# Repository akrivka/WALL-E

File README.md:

# WALL-E

For Blacker Hovse Ditch Day 2024 (Caltech tradition), we built a ~70% "real-life" size WALL-E robot, that could be **driven remotely with a PS5 controller, move his head and arms, record and transmit a video feed, speak (faintly)**, and he even had a small storage space in his body (for trash of course!).

Here's my video of him when he was at his best (he's currently sitting in a closet in Blacker to be used as a static showcase project, while I study over in Switzerland...): 

https://github.com/user-attachments/assets/6cdb80cf-8617-4d74-ad6d-1ea3f1ae313b

The model we used was https://www.thingiverse.com/thing:3703555, but we scaled it up by 5/3 which introduced a bunch of challenges. 

**! This repository was used for code-sharing and does not aim to make this project repeatable. Maybe in the future...**

## (rough) List of parts

* Rapsberry Pi 4 (Bluetooth) on Ubuntu 22.04 with ROS2 Humble installed
* PS5 controller
* [RoboClaw 2x15A Motor controller](https://www.basicmicro.com/RoboClaw-2x15A-Motor-Controller_p_10.html)
* [5202 Yellow Jacket Planetary Gear Motor](https://www.gobilda.com/5202-series-yellow-jacket-planetary-gear-motor-26-9-1-ratio-24mm-length-6mm-d-shaft-223-rpm-36mm-gearbox-3-3-5v-encoder/)
* [TowerPro MG996R servos](https://towerpro.com.tw/product/mg996r/)
* [HiLetgo PCA9685 PWM Servo Motor Driver](http://www.hiletgo.com/ProductDetail/2152091.html)
* [Small USB speaker](https://www.amazon.com/shuley-Computer-Speaker-Portable-Sound-bar/dp/B09S3G99HS/ref=sr_1_1)
* some random webcam we found
* 1x 11.1V Zeee LiPo battery (for motor), 1x 7.4V Zee LiPo battery (for servos), some random powerbank (for RPi)

## Some more photos

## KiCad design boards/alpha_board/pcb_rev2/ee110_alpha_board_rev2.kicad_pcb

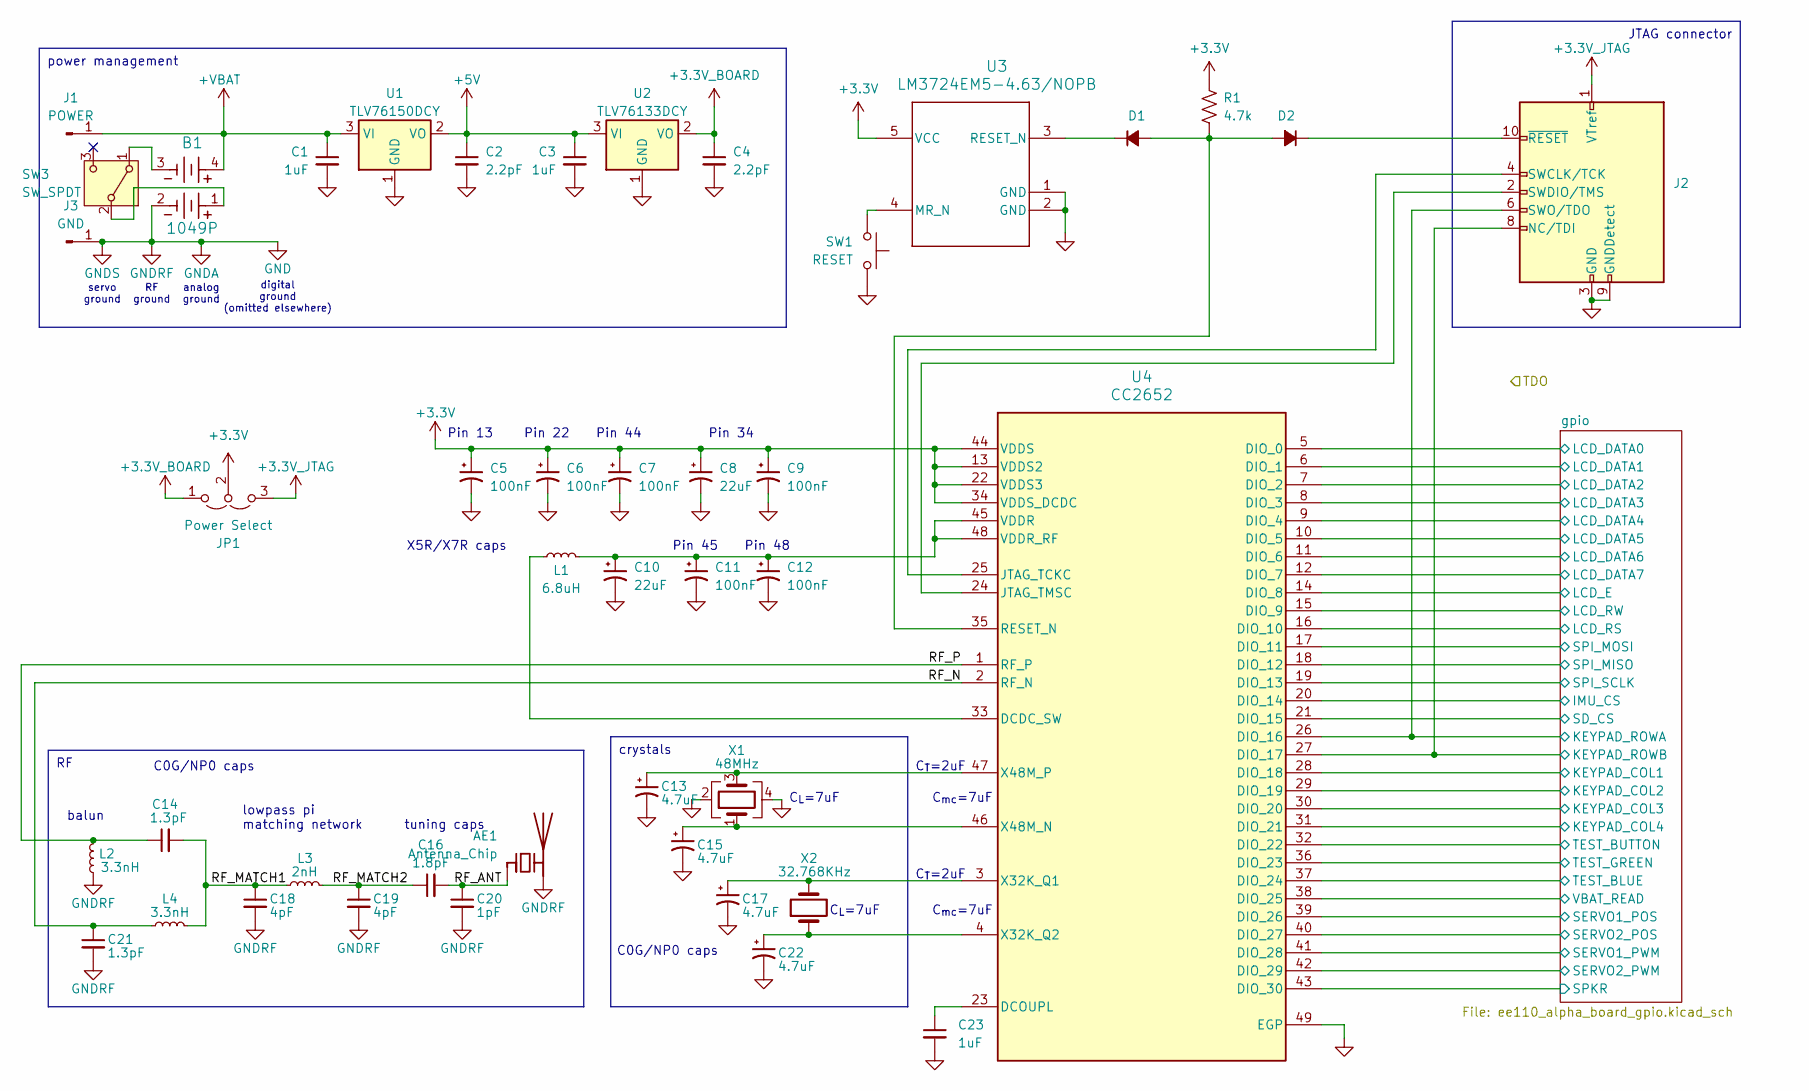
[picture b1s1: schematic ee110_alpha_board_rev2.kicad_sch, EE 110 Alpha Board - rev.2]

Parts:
AE1: Antenna_Chip; EE110_Antenna
B1: 1049P; 1049P_KEY
C1, C3, C23: 1uF; C_0805_2012Metric_Pad1.18x1.45mm_HandSolder
C2, C4: 2.2pF; C_0805_2012Metric_Pad1.18x1.45mm_HandSolder
C5, C6, C7, C9, C11, C12: 100nF; CP_EIA-2012-12_Kemet-R_Pad1.30x1.05mm_HandSolder
C8, C10: 22uF; CP_EIA-2012-12_Kemet-R_Pad1.30x1.05mm_HandSolder
C13, C15, C17, C22: 4.7uF; CP_EIA-2012-12_Kemet-R_Pad1.30x1.05mm_HandSolder
C14, C21: 1.3pF; C_0805_2012Metric_Pad1.18x1.45mm_HandSolder
C16: 1.8pF; C_0805_2012Metric_Pad1.18x1.45mm_HandSolder
C18, C19: 4pF; C_0805_2012Metric_Pad1.18x1.45mm_HandSolder
C20: 1pF; C_0805_2012Metric_Pad1.18x1.45mm_HandSolder
D1, D2: D_Small_Filled; D_SOD-323F
J1: POWER; 1pin
J2: Conn_ARM_JTAG_SWD_10; CON10_2X5_DUK_FTSH_SAI
J3: GND; 1pin
JP1: Power Select; 3pin_jumper
L1: 6.8uH; L_0805_2012Metric_Pad1.15x1.40mm_HandSolder
L2, L4: 3.3nH; L_0805_2012Metric_Pad1.15x1.40mm_HandSolder
L3: 2nH; L_0805_2012Metric_Pad1.15x1.40mm_HandSolder
R1: 4.7k; R_0805_2012Metric_Pad1.20x1.40mm_HandSolder
SW1: RESET; SW_SPST_TL3342
SW3: SW_SPDT; EG1903
U1: TLV76150DCY; SOT-223-3_TabPin2
U2: TLV76133DCY; SOT-223-3_TabPin2
U3: LM3724EM5-4.63/NOPB; SOT-23-5_HandSoldering
U4: CC2652; RGZ0048A_NV
X1: 48MHz; Crystal_SMD_5032-4Pin_5.0x3.2mm
X2: 32.768KHz; Crystal_SMD_3215-2Pin_3.2x1.5mm

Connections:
+3.3V: C5.1, C6.1, C7.1, C8.1, C9.1, JP1.2 (C), R1.1, U3.5 (VCC), U4.13 (VDDS2), U4.22 (VDDS3), U4.34 (VDDS_DCDC), U4.44 (VDDS); also elsewhere on the board
+3.3V_BOARD: C4.1, JP1.1 (A), U2.2 (VO)
+3.3V_JTAG: J2.1 (VTref), JP1.3 (B)
+5V: C2.1, C3.1, U1.2 (VO), U2.3 (VI); also elsewhere on the board
+VBAT: B1.4, C1.1, J1.1, U1.3 (VI); also elsewhere on the board
/RF_ANT: AE1.1 (FEED), C16.2, C20.1
/RF_MATCH1: C14.2, C18.1, L3.1, L4.2
/RF_MATCH2: C16.1, C19.1, L3.2
/RF_N: C21.1, L4.1, U4.2 (RF_N)
/RF_P: C14.1, L2.2, U4.1 (RF_P)
/gpio/IMU_CS: U4.20 (DIO_14); also elsewhere on the board
/gpio/KEYPAD_COL1: U4.28 (DIO_18); also elsewhere on the board
/gpio/KEYPAD_COL2: U4.29 (DIO_19); also elsewhere on the board
/gpio/KEYPAD_COL3: U4.30 (DIO_20); also elsewhere on the board
/gpio/KEYPAD_COL4: U4.31 (DIO_21); also elsewhere on the board
/gpio/KEYPAD_ROWA: J2.6 (SWO/TDO), U4.26 (DIO_16); also elsewhere on the board
/gpio/KEYPAD_ROWB: J2.8 (NC/TDI), U4.27 (DIO_17); also elsewhere on the board
/gpio/LCD_DATA0: U4.5 (DIO_0); also elsewhere on the board
/gpio/LCD_DATA1: U4.6 (DIO_1); also elsewhere on the board
/gpio/LCD_DATA2: U4.7 (DIO_2); also elsewhere on the board
/gpio/LCD_DATA3: U4.8 (DIO_3); also elsewhere on the board
/gpio/LCD_DATA4: U4.9 (DIO_4); also elsewhere on the board
/gpio/LCD_DATA5: U4.10 (DIO_5); also elsewhere on the board
/gpio/LCD_DATA6: U4.11 (DIO_6); also elsewhere on the board
/gpio/LCD_DATA7: U4.12 (DIO_7); also elsewhere on the board
/gpio/LCD_E: U4.14 (DIO_8); also elsewhere on the board
/gpio/LCD_RS: U4.16 (DIO_10); also elsewhere on the board
/gpio/LCD_RW: U4.15 (DIO_9); also elsewhere on the board
/gpio/SD_CS: U4.21 (DIO_15); also elsewhere on the board
/gpio/SERVO1_POS: U4.39 (DIO_26); also elsewhere on the board
/gpio/SERVO1_PWM: U4.41 (DIO_28); also elsewhere on the board
/gpio/SERVO2_POS: U4.40 (DIO_27); also elsewhere on the board
/gpio/SERVO2_PWM: U4.42 (DIO_29); also elsewhere on the board
/gpio/SPI_MISO: U4.18 (DIO_12); also elsewhere on the board
/gpio/SPI_MOSI: U4.17 (DIO_11); also elsewhere on the board
/gpio/SPI_SCLK: U4.19 (DIO_13); also elsewhere on the board
/gpio/SPKR: U4.43 (DIO_30); also elsewhere on the board
/gpio/TEST_BLUE: U4.37 (DIO_24); also elsewhere on the board
/gpio/TEST_BUTTON: U4.32 (DIO_22); also elsewhere on the board
/gpio/TEST_GREEN: U4.36 (DIO_23); also elsewhere on the board
/gpio/VBAT_READ: U4.38 (DIO_25); also elsewhere on the board
GND: AE1.2 (PCB_Trace), B1.2, C1.2, C2.2, C3.2, C4.2, C5.2, C6.2, C7.2, C8.2, C9.2, C10.2, C11.2, C12.2, C13.2, C15.2, C17.2, C18.2, C19.2, C20.2, C21.2, C22.2, C23.2, J2.3 (GND), J2.5 (GND), J2.9 (GNDDetect), J3.1, L2.1, SW1.2, U1.1 (GND), U2.1 (GND), U3.1 (GND), U3.2 (GND), U4.49 (EGP), X1.2, X1.4; also elsewhere on the board
unnamed: D1.2 (A), D2.2 (A), R1.2, U4.35 (RESET_N)
unnamed: D1.1 (K), U3.3 (RESET_N)
unnamed: D2.1 (K), J2.10 (~RESET)
unnamed: J2.4 (SWCLK/TCK), U4.25 (JTAG_TCKC)
unnamed: J2.2 (SWDIO/TMS), U4.24 (JTAG_TMSC)
unnamed: B1.3, SW3.1 (A)
unnamed: B1.1, SW3.2 (B)
unnamed: SW1.1, U3.4 (MR_N)
unnamed: L1.1, U4.33 (DCDC_SW)
unnamed: C23.1, U4.23 (DCOUPL)
unnamed: C10.1, C11.1, C12.1, L1.2, U4.45 (VDDR), U4.48 (VDDR_RF)
unnamed: C17.1, U4.3 (X32K_Q1), X2.2
unnamed: C22.1, U4.4 (X32K_Q2), X2.1
unnamed: C15.1, U4.46 (X48M_N), X1.1
unnamed: C13.1, U4.47 (X48M_P), X1.3

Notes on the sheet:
power management
JTAG connector
crystals
Pin 22
C_{mc}=7uF
tuning caps
Pin 44
lowpass pi matching network
C0G/NP0 caps
X5R/X7R caps
C_{T}=2uF
RF ground
Pin 48
Pin 45
C_{L}=7uF
Pin 34
servo ground
analog ground
digital ground (omitted elsewhere)
Pin 13
balun

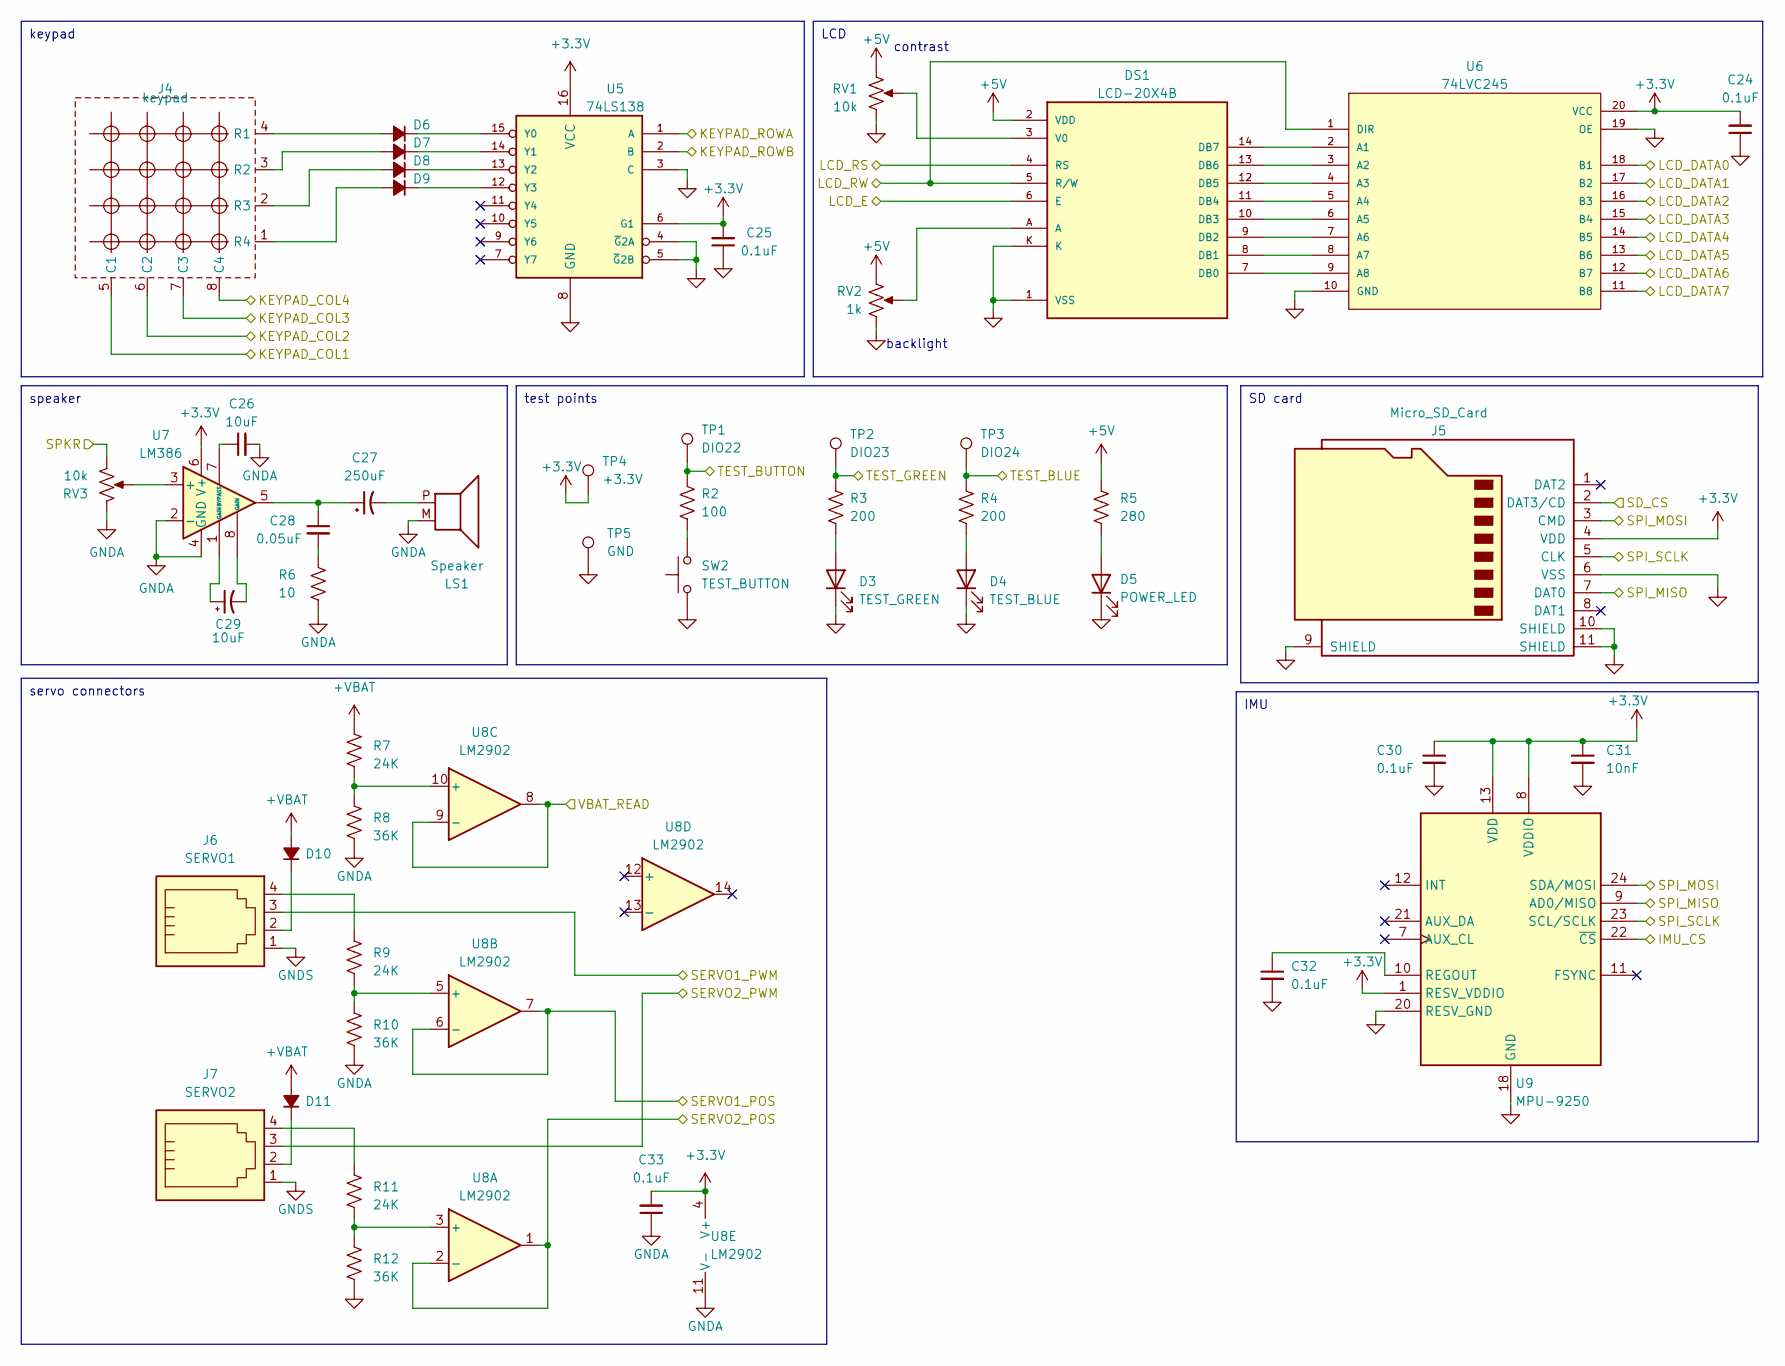
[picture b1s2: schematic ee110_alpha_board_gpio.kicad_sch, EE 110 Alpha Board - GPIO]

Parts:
C24, C25, C30, C32, C33: 0.1uF; C_0805_2012Metric_Pad1.18x1.45mm_HandSolder
C26: 10uF; C_0805_2012Metric_Pad1.18x1.45mm_HandSolder
C27: 250uF; CP_EIA-2012-12_Kemet-R_Pad1.30x1.05mm_HandSolder
C28: 0.05uF; C_0805_2012Metric_Pad1.18x1.45mm_HandSolder
C29: 10uF; CP_EIA-2012-12_Kemet-R_Pad1.30x1.05mm_HandSolder
C31: 10nF; C_0805_2012Metric_Pad1.18x1.45mm_HandSolder
D3: TEST_GREEN; LED_0805_2012Metric_Pad1.15x1.40mm_HandSolder
D4: TEST_BLUE; LED_0805_2012Metric_Pad1.15x1.40mm_HandSolder
D5: POWER_LED; LED_D3.0mm
D6, D7, D8, D9: D_Small_Filled; D_SOD-323F
D10, D11: D_Small_Filled; D_DO-15_P12.70mm_Horizontal
DS1: LCD-20X4B; WINSTAR-WH1604A; PARTREV N/A
J4: keypad; 4x4_Keypad
J5: Micro_SD_Card; microSD_HC_Hirose_DM3D-SF
J6: SERVO1; JST_XH_S4B-XH-A-1_1x04_P2.50mm_Horizontal
J7: SERVO2; JST_XH_S4B-XH-A-1_1x04_P2.50mm_Horizontal
LS1: Speaker; SPKR_CVS-1508
R2: 100; R_0805_2012Metric_Pad1.20x1.40mm_HandSolder
R3, R4: 200; R_0805_2012Metric_Pad1.20x1.40mm_HandSolder
R5: 280; R_0805_2012Metric_Pad1.20x1.40mm_HandSolder
R6: 10; R_0805_2012Metric_Pad1.20x1.40mm_HandSolder
R7, R9, R11: 24K; R_0805_2012Metric_Pad1.20x1.40mm_HandSolder
R8, R10, R12: 36K; R_0805_2012Metric_Pad1.20x1.40mm_HandSolder
RV1, RV3: 10k; Potentiometer_Bourns_3296P_Horizontal
RV2: 1k; Potentiometer_Bourns_3296P_Horizontal
SW2: TEST_BUTTON; SW_SPST_TL3342
TP1: DIO22; TestPoint_THTPad_2.0x2.0mm_Drill1.0mm
TP2: DIO23; TestPoint_THTPad_2.0x2.0mm_Drill1.0mm
TP3: DIO24; TestPoint_THTPad_2.0x2.0mm_Drill1.0mm
TP4: +3.3V; TestPoint_THTPad_2.0x2.0mm_Drill1.0mm
TP5: GND; TestPoint_THTPad_2.0x2.0mm_Drill1.0mm
U5: 74LS138; SOIC-16_3.9x9.9mm_P1.27mm
U6: 74LVC245; SOIC-20W_7.5x15.4mm_P1.27mm
U7: LM386; DIP-8_W7.62mm
U8: LM2902; SOIC-14_3.9x8.7mm_P1.27mm
U9: MPU-9250; QFN-24-1EP_3x3mm_P0.4mm_EP1.75x1.6mm

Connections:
+3.3V: C24.2, C25.2, C30.1, C31.1, C33.2, J5.4 (VDD), TP4.1, U5.6 (G1), U5.16 (VCC), U6.20 (VCC), U7.6 (V+), U8.4 (V+), U9.1 (RESV_VDDIO), U9.8 (VDDIO), U9.13 (VDD); also elsewhere on the board
+5V: DS1.2 (VDD), R5.1, RV1.1, RV2.1; also elsewhere on the board
+VBAT: D10.2 (A), D11.2 (A), R7.1; also elsewhere on the board
/gpio/IMU_CS: U9.22 (~CS); also elsewhere on the board
/gpio/KEYPAD_COL1: J4.5 (C1); also elsewhere on the board
/gpio/KEYPAD_COL2: J4.6 (C2); also elsewhere on the board
/gpio/KEYPAD_COL3: J4.7 (C3); also elsewhere on the board
/gpio/KEYPAD_COL4: J4.8 (C4); also elsewhere on the board
/gpio/KEYPAD_ROWA: U5.1 (A); also elsewhere on the board
/gpio/KEYPAD_ROWB: U5.2 (B); also elsewhere on the board
/gpio/LCD_DATA0: U6.18 (B1); also elsewhere on the board
/gpio/LCD_DATA1: U6.17 (B2); also elsewhere on the board
/gpio/LCD_DATA2: U6.16 (B3); also elsewhere on the board
/gpio/LCD_DATA3: U6.15 (B4); also elsewhere on the board
/gpio/LCD_DATA4: U6.14 (B5); also elsewhere on the board
/gpio/LCD_DATA5: U6.13 (B6); also elsewhere on the board
/gpio/LCD_DATA6: U6.12 (B7); also elsewhere on the board
/gpio/LCD_DATA7: U6.11 (B8); also elsewhere on the board
/gpio/LCD_E: DS1.6 (E); also elsewhere on the board
/gpio/LCD_RS: DS1.4 (RS); also elsewhere on the board
/gpio/LCD_RW: DS1.5 (R/W), U6.1 (DIR); also elsewhere on the board
/gpio/SD_CS: J5.2 (DAT3/CD); also elsewhere on the board
/gpio/SERVO1_POS: U8.6 (-), U8.7; also elsewhere on the board
/gpio/SERVO1_PWM: J6.3; also elsewhere on the board
/gpio/SERVO2_POS: U8.1, U8.2 (-); also elsewhere on the board
/gpio/SERVO2_PWM: J7.3; also elsewhere on the board
/gpio/SPI_MISO: J5.7 (DAT0), U9.9 (AD0/MISO); also elsewhere on the board
/gpio/SPI_MOSI: J5.3 (CMD), U9.24 (SDA/MOSI); also elsewhere on the board
/gpio/SPI_SCLK: J5.5 (CLK), U9.23 (SCL/SCLK); also elsewhere on the board
/gpio/SPKR: RV3.3; also elsewhere on the board
/gpio/TEST_BLUE: R4.2, TP3.1; also elsewhere on the board
/gpio/TEST_BUTTON: R2.2, TP1.1; also elsewhere on the board
/gpio/TEST_GREEN: R3.2, TP2.1; also elsewhere on the board
/gpio/VBAT_READ: U8.8, U8.9 (-); also elsewhere on the board
GND: C24.1, C25.1, C26.2, C30.2, C31.2, C32.2, C33.1, D3.1 (K), D4.1 (K), D5.1 (K), DS1.1 (VSS), DS1.K, J5.6 (VSS), J5.9 (SHIELD), J5.10 (SHIELD), J5.11 (SHIELD), J6.1, J7.1, LS1.M (2), R6.2, R8.2, R10.2, R12.2, RV1.3, RV2.3, RV3.1, SW2.1, TP5.1, U5.3 (C), U5.4 (~G2A), U5.5 (~G2B), U5.8 (GND), U6.10 (GND), U6.19 (OE), U7.2 (-), U7.4 (GND), U8.11 (V-), U9.18 (GND), U9.20 (RESV_GND); also elsewhere on the board
unnamed: C27.1, C28.1, U7.5
unnamed: C28.2, R6.1
unnamed: C29.1, U7.1 (GAIN)
unnamed: C29.2, U7.8 (GAIN)
unnamed: D3.2 (A), R3.1
unnamed: D4.2 (A), R4.1
unnamed: D5.2 (A), R5.2
unnamed: D6.2 (A), J4.4 (R1)
unnamed: D6.1 (K), U5.15 (Y0)
unnamed: D7.2 (A), J4.3 (R2)
unnamed: D7.1 (K), U5.14 (Y1)
unnamed: D8.2 (A), J4.2 (R3)
unnamed: D8.1 (K), U5.13 (Y2)
unnamed: D9.2 (A), J4.1 (R4)
unnamed: D9.1 (K), U5.12 (Y3)
unnamed: D10.1 (K), J6.2
unnamed: D11.1 (K), J7.2
unnamed: DS1.7 (DB0), U6.9 (A8)
unnamed: DS1.8 (DB1), U6.8 (A7)
unnamed: DS1.9 (DB2), U6.7 (A6)
unnamed: DS1.10 (DB3), U6.6 (A5)
unnamed: DS1.11 (DB4), U6.5 (A4)
unnamed: DS1.12 (DB5), U6.4 (A3)
unnamed: DS1.13 (DB6), U6.3 (A2)
unnamed: DS1.14 (DB7), U6.2 (A1)
unnamed: DS1.A, RV2.2
unnamed: DS1.3 (V0), RV1.2
unnamed: J6.4, R9.1
unnamed: J7.4, R11.1
unnamed: C27.2, LS1.P (1)
unnamed: R2.1, SW2.2
unnamed: RV3.2, U7.3 (+)
unnamed: C26.1, U7.7 (BYPASS)
unnamed: R11.2, R12.1, U8.3 (+)
unnamed: R9.2, R10.1, U8.5 (+)
unnamed: R7.2, R8.1, U8.10 (+)
unnamed: C32.1, U9.10 (REGOUT)

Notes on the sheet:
keypad
SD card
servo connectors
speaker
test points
LCD
IMU
backlight
contrast

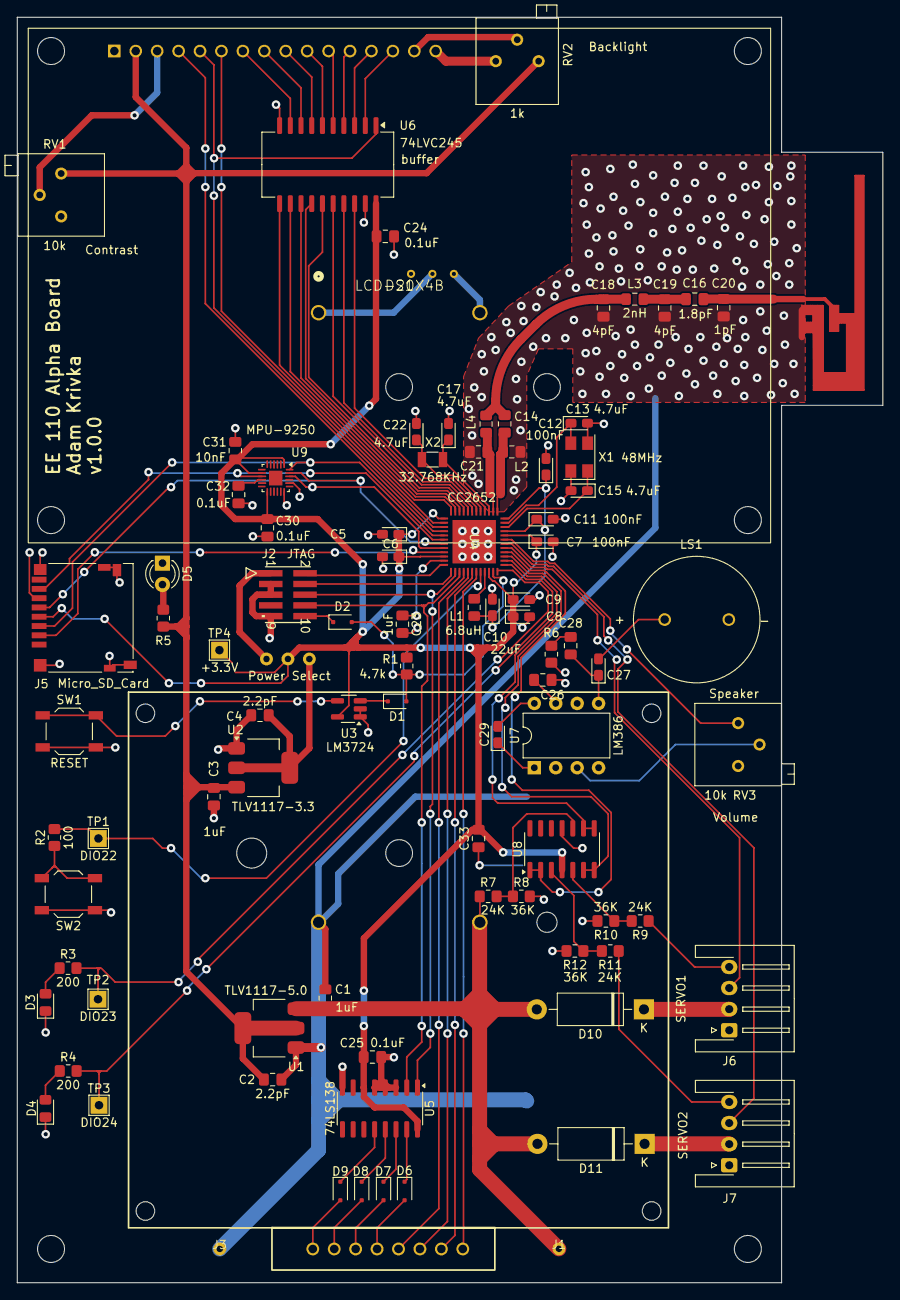
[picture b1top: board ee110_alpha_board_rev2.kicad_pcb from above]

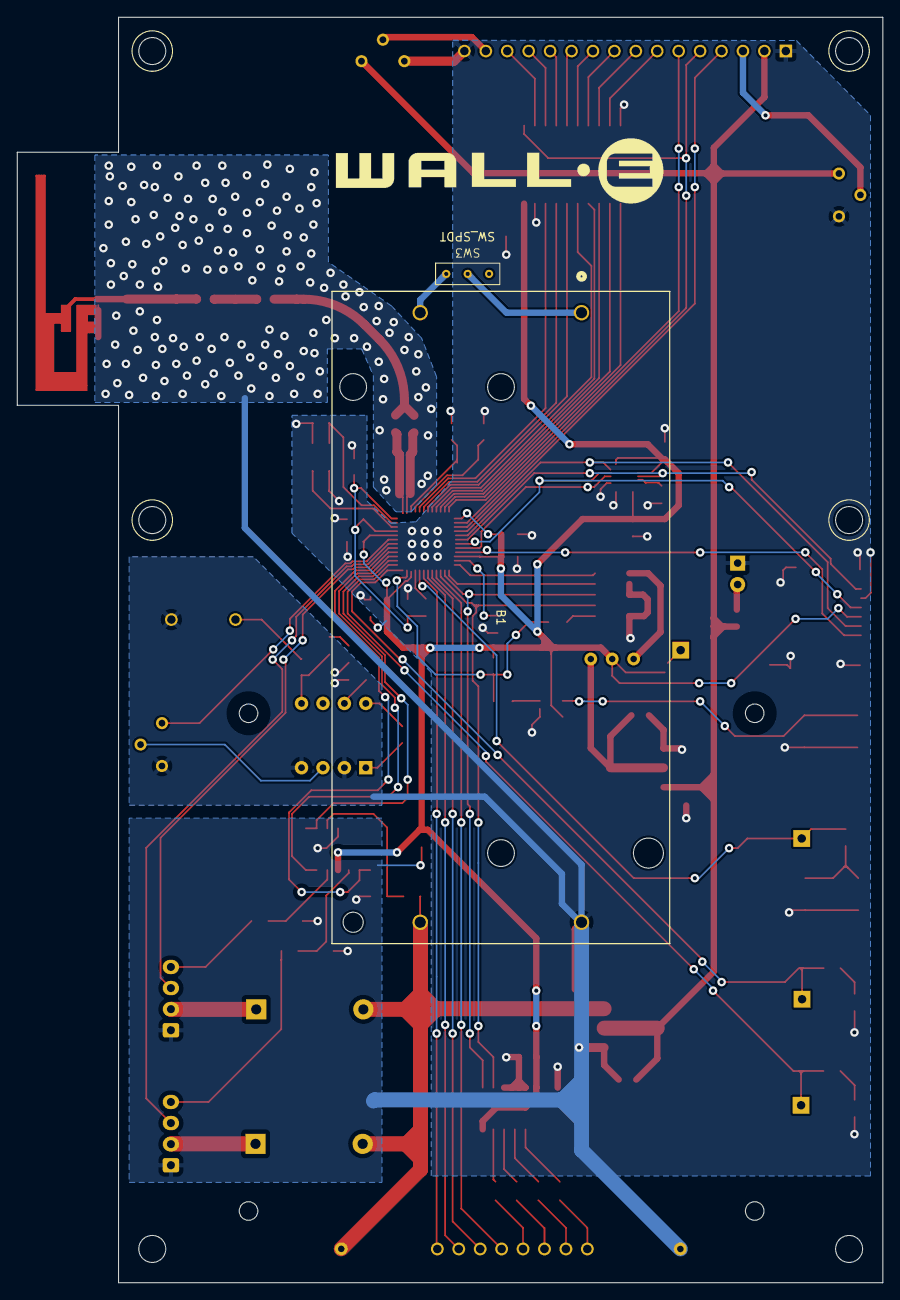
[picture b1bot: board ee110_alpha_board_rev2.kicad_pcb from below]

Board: 2 copper layers, 102.6 x 150.0 mm, 93 parts (2 on the bottom side), 94 nets.

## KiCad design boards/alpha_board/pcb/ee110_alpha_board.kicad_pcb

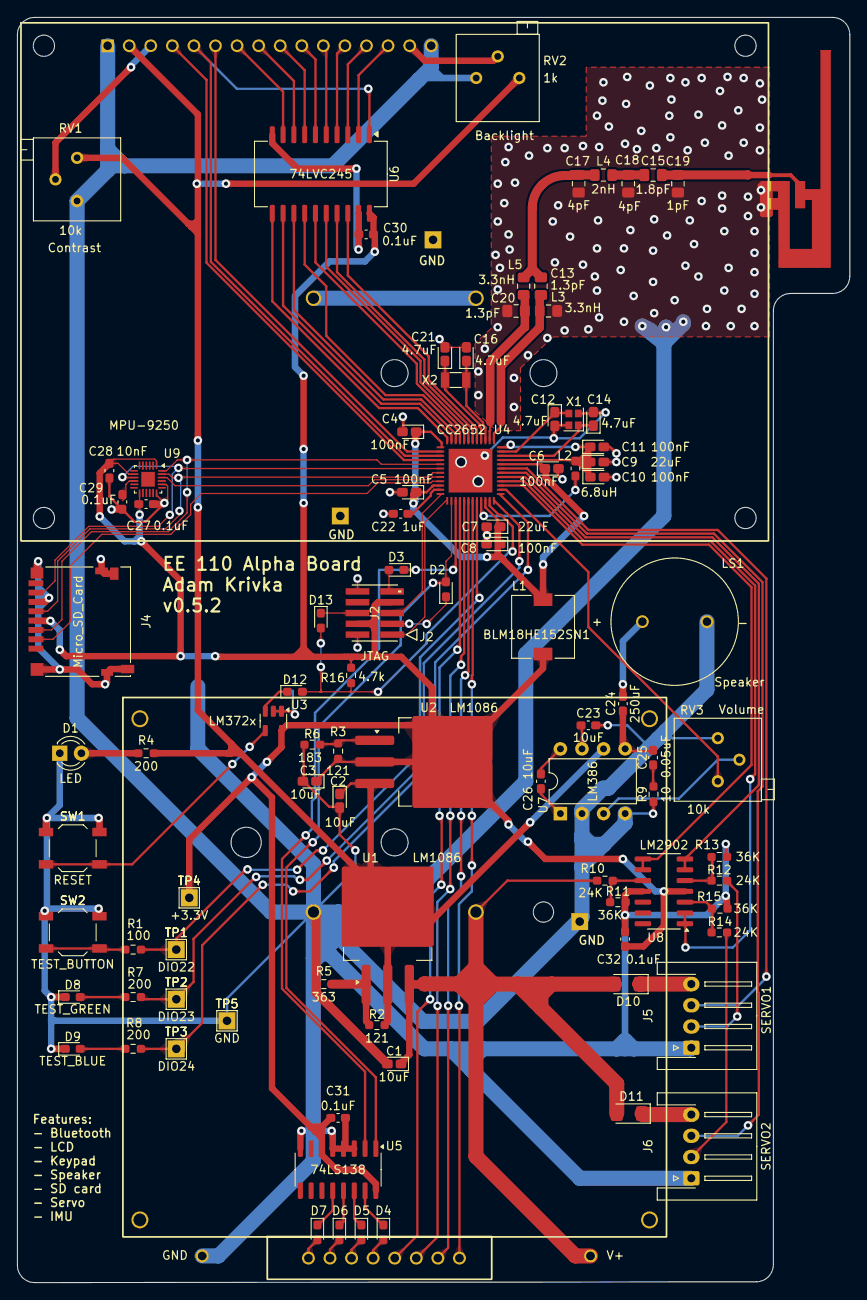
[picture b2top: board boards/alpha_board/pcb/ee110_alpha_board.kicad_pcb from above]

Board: 2 copper layers, 98.0 x 149.0 mm, 97 parts (1 on the bottom side), 96 nets.

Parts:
AE1: Antenna_Chip; EE110_Antenna
B1: 1049P; 1049P_KEY
C1, C2, C3: 10uF; CP_EIA-1608-08_AVX-J_Pad1.25x1.05mm_HandSolder
C4, C5, C6, C8, C10, C11: 100nF; CP_EIA-1608-08_AVX-J_Pad1.25x1.05mm_HandSolder
C7, C9: 22uF; CP_EIA-1608-08_AVX-J_Pad1.25x1.05mm_HandSolder
C12, C14, C16, C21: 4.7uF; CP_EIA-1608-08_AVX-J_Pad1.25x1.05mm_HandSolder
C13, C20: 1.3pF; C_0805_2012Metric_Pad1.18x1.45mm_HandSolder
C15: 1.8pF; C_0805_2012Metric_Pad1.18x1.45mm_HandSolder
C17, C18: 4pF; C_0805_2012Metric_Pad1.18x1.45mm_HandSolder
C19: 1pF; C_0805_2012Metric_Pad1.18x1.45mm_HandSolder
C22: 1uF; C_0603_1608Metric_Pad1.08x0.95mm_HandSolder
C23, C26: 10uF; C_0603_1608Metric_Pad1.08x0.95mm_HandSolder
C24: 250uF; C_0603_1608Metric_Pad1.08x0.95mm_HandSolder
C25: 0.05uF; C_0603_1608Metric_Pad1.08x0.95mm_HandSolder
C27, C29, C30, C31, C32: 0.1uF; C_0603_1608Metric_Pad1.08x0.95mm_HandSolder
C28: 10nF; C_0603_1608Metric_Pad1.08x0.95mm_HandSolder
D1: LED; LED_D3.0mm
D2, D3, D4, D5, D6, D7, D12, D13: D_Small_Filled; D_0603_1608Metric_Pad1.05x0.95mm_HandSolder
D8: TEST_GREEN; LED_0603_1608Metric_Pad1.05x0.95mm_HandSolder
D9: TEST_BLUE; LED_0603_1608Metric_Pad1.05x0.95mm_HandSolder
D10, D11: D_Small_Filled; D_1206_3216Metric_Pad1.42x1.75mm_HandSolder
DS1: LCD-20X4B; WINSTAR-WH1604A
J1: power; My_Power_Connector
J2: JTAG; CON10_2X5_DUK_FTSH_SAI
J3: 4x4_Keypad
J4: Micro_SD_Card; microSD_HC_Hirose_DM3D-SF
J5: SERVO1; JST_XH_S4B-XH-A-1_1x04_P2.50mm_Horizontal
J6: SERVO2; JST_XH_S4B-XH-A-1_1x04_P2.50mm_Horizontal
L1: BLM18HE152SN1; L_7.3x7.3_H3.5
L2: 6.8uH; L_0603_1608Metric_Pad1.05x0.95mm_HandSolder
L3, L5: 3.3nH; L_0805_2012Metric_Pad1.15x1.40mm_HandSolder
L4: 2nH; L_0805_2012Metric_Pad1.15x1.40mm_HandSolder
LS1: Speaker; SPKR_CVS-1508
R1: 100; R_0603_1608Metric_Pad0.98x0.95mm_HandSolder
R2, R3: 121; R_0603_1608Metric_Pad0.98x0.95mm_HandSolder
R4, R7, R8: 200; R_0603_1608Metric_Pad0.98x0.95mm_HandSolder
R5: 363; R_0603_1608Metric_Pad0.98x0.95mm_HandSolder
R6: 183; R_0603_1608Metric_Pad0.98x0.95mm_HandSolder
R9: 10; R_0603_1608Metric_Pad0.98x0.95mm_HandSolder
R10, R12, R14: 24K; R_0603_1608Metric_Pad0.98x0.95mm_HandSolder
R11, R13, R15: 36K; R_0603_1608Metric_Pad0.98x0.95mm_HandSolder
R16: 4.7k; R_0603_1608Metric_Pad0.98x0.95mm_HandSolder
RV1, RV3: 10k; Potentiometer_Bourns_3296P_Horizontal
RV2: 1k; Potentiometer_Bourns_3296P_Horizontal
SW1: RESET; SW_SPST_TL3342
SW2: TEST_BUTTON; SW_SPST_TL3342
TP1: DIO22; TestPoint_THTPad_2.0x2.0mm_Drill1.0mm
TP2: DIO23; TestPoint_THTPad_2.0x2.0mm_Drill1.0mm
TP3: DIO24; TestPoint_THTPad_2.0x2.0mm_Drill1.0mm
TP4: +3.3V; TestPoint_THTPad_2.0x2.0mm_Drill1.0mm
TP5: GND; TestPoint_THTPad_2.0x2.0mm_Drill1.0mm
U1, U2: LM1086; TO-263-3_TabPin2
U3: LM372x; SOT-23-5
U4: CC2652; RGZ0048A_NV
U5: 74LS138; SOIC-16_3.9x9.9mm_P1.27mm
U6: 74LVC245; SOIC-20W_7.5x15.4mm_P1.27mm
U7: LM386; DIP-8_W7.62mm
U8: LM2902; SOIC-14_3.9x8.7mm_P1.27mm
U9: MPU-9250; QFN-24-1EP_3x3mm_P0.4mm_EP1.75x1.6mm
X1: 48MHz; Crystal_SMD_2016-4Pin_2.0x1.6mm
X2: 32.768KHz; Crystal_SMD_3215-2Pin_3.2x1.5mm

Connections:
+3.3V: C3.1, C27.1, C28.1, C30.2, C31.2, C32.2, J2.4 (VREF), J2.7 (VCC), J4.4 (VDD), L1.1, R3.1, R16.1, TP4.1, U2.2 (VO), U3.5 (Vcc), U5.6 (G1), U5.16 (VCC), U6.20 (VCC), U8.4 (V+), U9.1 (RESV_VDDIO), U9.8 (VDDIO), U9.13 (VDD)
+5V: C2.1, DS1.2 (VDD), R2.1, R4.1, RV1.1, RV2.1, U1.2 (VO), U2.3 (VI), U7.6 (V+)
+VBAT: B1.4, C1.1, D10.2 (A), D11.2 (A), J1.1, R10.1, U1.3 (VI)
/RF_ANT: AE1.1 (FEED), C15.2, C19.1
/RF_MATCH1: C13.2, C17.1, L4.1, L5.2
/RF_MATCH2: C15.1, C18.1, L4.2
/RF_N: C20.1, L5.1, U4.2 (RF_N)
/RF_P: C13.1, L3.2, U4.1 (RF_P)
/gpio/IMU_CS: U4.20 (DIO_14), U9.22 (~CS)
/gpio/KEYPAD_COL1: J3.5 (C1), U4.28 (DIO_18)
/gpio/KEYPAD_COL2: J3.6 (C2), U4.29 (DIO_19)
/gpio/KEYPAD_COL3: J3.7 (C3), U4.30 (DIO_20)
/gpio/KEYPAD_COL4: J3.8 (C4), U4.31 (DIO_21)
/gpio/KEYPAD_ROWA: D2.2 (A), U4.26 (DIO_16), U5.1 (A)
/gpio/KEYPAD_ROWB: D3.1 (K), U4.27 (DIO_17), U5.2 (B)
/gpio/LCD_DATA0: U4.5 (DIO_0), U6.18 (B1)
/gpio/LCD_DATA1: U4.6 (DIO_1), U6.17 (B2)
/gpio/LCD_DATA2: U4.7 (DIO_2), U6.16 (B3)
/gpio/LCD_DATA3: U4.8 (DIO_3), U6.15 (B4)
/gpio/LCD_DATA4: U4.9 (DIO_4), U6.14 (B5)
/gpio/LCD_DATA5: U4.10 (DIO_5), U6.13 (B6)
/gpio/LCD_DATA6: U4.11 (DIO_6), U6.12 (B7)
/gpio/LCD_DATA7: U4.12 (DIO_7), U6.11 (B8)
/gpio/LCD_E: DS1.6 (E), U4.14 (DIO_8)
/gpio/LCD_RS: DS1.4 (RS), U4.16 (DIO_10)
/gpio/LCD_RW: DS1.5 (R/W), U4.15 (DIO_9), U6.1 (DIR)
/gpio/SD_CS: J4.2 (DAT3/CD), U4.21 (DIO_15)
/gpio/SERVO1_POS: U4.41 (DIO_28), U8.6 (-), U8.7
/gpio/SERVO1_PWM: J5.3, U4.43 (DIO_30)
/gpio/SERVO2_POS: U4.40 (DIO_27), U8.1, U8.2 (-)
/gpio/SERVO2_PWM: J6.3, U4.42 (DIO_29)
/gpio/SPI_MISO: J4.7 (DAT0), U4.18 (DIO_12), U9.9 (AD0/MISO)
/gpio/SPI_MOSI: J4.3 (CMD), U4.17 (DIO_11), U9.24 (SDA/MOSI)
/gpio/SPI_SCLK: J4.5 (CLK), U4.19 (DIO_13), U9.23 (SCL/SCLK)
/gpio/SPKR: RV3.1, U4.38 (DIO_25)
/gpio/TEST_BLUE: R8.2, TP3.1, U4.37 (DIO_24)
/gpio/TEST_BUTTON: R1.2, TP1.1, U4.32 (DIO_22)
/gpio/TEST_GREEN: R7.2, TP2.1, U4.36 (DIO_23)
/gpio/VBAT_READ: U4.39 (DIO_26), U8.8, U8.9 (-)
GND: AE1.2 (PCB_Trace), B1.2, C1.2, C2.2, C3.2, C4.2, C5.2, C6.2, C7.2, C8.2, C9.2, C10.2, C11.2, C12.2, C14.2, C16.2, C17.2, C18.2, C19.2, C20.2, C21.2, C22.2, C23.2, C27.2, C28.2, C29.2, C30.1, C31.1, C32.1, D1.1 (K), D8.1 (K), D9.1 (K), DS1.1 (VSS), DS1.K, J1.2, J2.2 (GND), J2.10 (GND), J4.6 (VSS), J4.9 (SHIELD), J4.10 (SHIELD), J4.11 (SHIELD), J5.1, J6.1, L3.1, LS1.M (2), R5.2, R6.2, R9.2, R11.2, R13.2, R15.2, RV1.3, RV2.3, RV3.3, SW1.1, SW2.1, TP5.1, U3.1 (GND), U3.2 (GND), U4.49 (EGP), U5.3 (C), U5.4 (~G2A), U5.5 (~G2B), U5.8 (GND), U6.10 (GND), U6.19 (OE), U7.2 (-), U7.4 (GND), U8.11 (V-), U9.18 (GND), U9.20 (RESV_GND), X1.2, X1.4
unnamed: B1.1, B1.3
unnamed: C24.1, C25.1, U7.5
unnamed: C25.2, R9.1
unnamed: C26.1, U7.1 (GAIN)
unnamed: C26.2, U7.8 (GAIN)
unnamed: D1.2 (A), R4.2
unnamed: D2.1 (K), J2.3 (TDO)
unnamed: D3.2 (A), J2.9 (TDI)
unnamed: D4.2 (A), J3.4 (R1)
unnamed: D4.1 (K), U5.15 (Y0)
unnamed: D5.2 (A), J3.3 (R2)
unnamed: D5.1 (K), U5.14 (Y1)
unnamed: D6.2 (A), J3.2 (R3)
unnamed: D6.1 (K), U5.13 (Y2)
unnamed: D7.2 (A), J3.1 (R4)
unnamed: D7.1 (K), U5.12 (Y3)
unnamed: D8.2 (A), R7.1
unnamed: D9.2 (A), R8.1
unnamed: D10.1 (K), J5.4
unnamed: D11.1 (K), J6.4
unnamed: D12.2 (A), D13.2 (A), R16.2, U4.35 (RESET_N)
unnamed: D12.1 (K), U3.3 (RESET)
unnamed: D13.1 (K), J2.6 (~SRST)
unnamed: DS1.7 (DB0), U6.9 (A8)
unnamed: DS1.8 (DB1), U6.8 (A7)
unnamed: DS1.9 (DB2), U6.7 (A6)
unnamed: DS1.10 (DB3), U6.6 (A5)
unnamed: DS1.11 (DB4), U6.5 (A4)
unnamed: DS1.12 (DB5), U6.4 (A3)
unnamed: DS1.13 (DB6), U6.3 (A2)
unnamed: DS1.14 (DB7), U6.2 (A1)
unnamed: DS1.A, RV2.2
unnamed: DS1.3 (V0), RV1.2
unnamed: J2.1 (TCK), U4.25 (JTAG_TCKC)
unnamed: J2.5 (TMS), U4.24 (JTAG_TMSC)
unnamed: J5.2, R12.1
unnamed: J6.2, R14.1
unnamed: C24.2, LS1.P (1)
unnamed: R1.1, SW2.2
unnamed: R2.2, R5.1, U1.1 (GND)
unnamed: R3.2, R6.1, U2.1 (GND)
unnamed: SW1.2, U3.4 (MR)
unnamed: L2.1, U4.33 (DCDC_SW)
unnamed: C22.1, U4.23 (DCOUPL)
unnamed: C9.1, C10.1, C11.1, L2.2, U4.45 (VDDR), U4.48 (VDDR_RF)
unnamed: C4.1, C5.1, C6.1, C7.1, C8.1, L1.2, U4.13 (VDDS2), U4.22 (VDDS3), U4.34 (VDDS_DCDC), U4.44 (VDDS)
unnamed: C16.1, U4.3 (X32K_Q1), X2.2
unnamed: C21.1, U4.4 (X32K_Q2), X2.1
unnamed: C14.1, U4.46 (X48M_N), X1.1
unnamed: C12.1, U4.47 (X48M_P), X1.3
unnamed: RV3.2, U7.3 (+)
unnamed: C23.1, U7.7 (BYPASS)
unnamed: R14.2, R15.1, U8.3 (+)
unnamed: R12.2, R13.1, U8.5 (+)
unnamed: R10.2, R11.1, U8.10 (+)
unnamed: C29.1, U9.10 (REGOUT)
